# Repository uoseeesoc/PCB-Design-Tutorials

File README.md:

# PCB-Design-Tutorials
This is the repository for the EEE Society PCB Design Tutorials using KiCAD. All of the lecture material and examples can be found here. These sessions were run during the Summer Term of the 2018/19 academic year.

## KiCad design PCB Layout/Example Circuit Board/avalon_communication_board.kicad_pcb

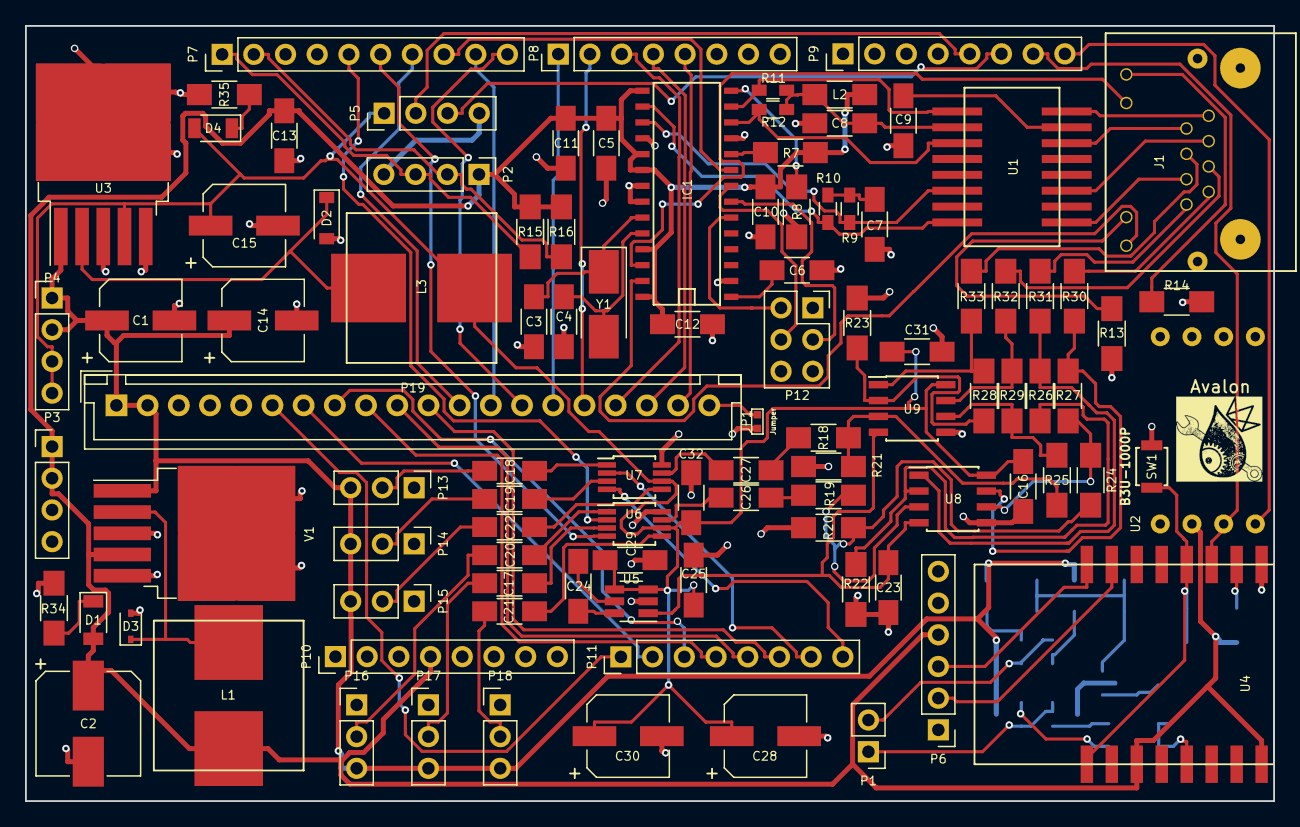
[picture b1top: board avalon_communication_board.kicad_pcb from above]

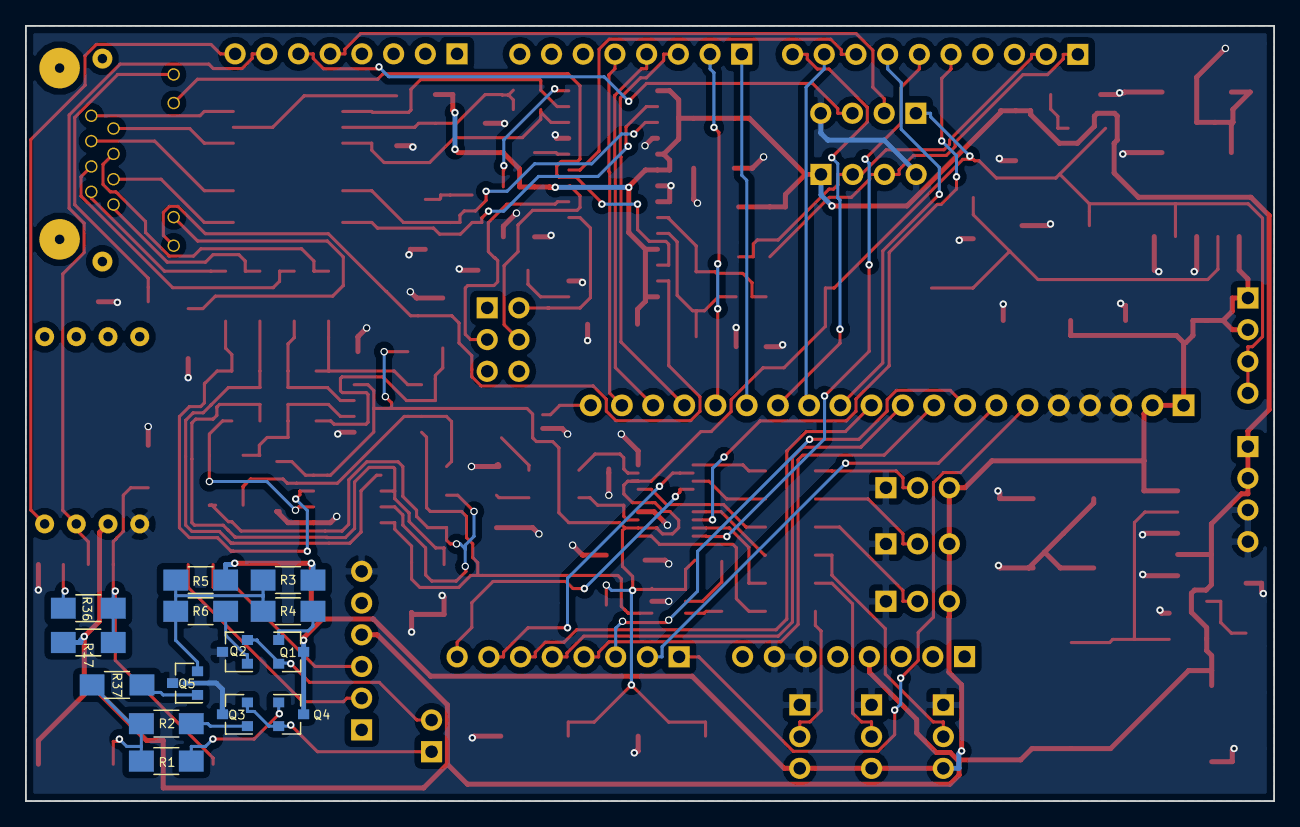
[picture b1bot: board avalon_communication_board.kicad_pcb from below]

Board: 4 copper layers, 100.0 x 62.1 mm, 115 parts (14 on the bottom side), 103 nets.

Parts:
C1, C14: 100uF; CP_Elec_6.3x7.7
C2: 1000uF; CP_Elec_8x10
C3, C4: 18pF; C_1206_HandSoldering
C5, C10, C11, C12, C17, C18, C19, C20, C21, C22, C25, C29, C31, C32: 0.1uF; C_1206_HandSoldering
C6: 10uF; C_1206_HandSoldering
C7, C8: 10nF; C_1206_HandSoldering
C9: 1nF; C_1206_HandSoldering
C13: 100nF; C_1206_HandSoldering
C15: 330uF; CP_Elec_6.3x7.7
C16, C23: 2.2uF; C_1206_HandSoldering
C24: 1uF; C_1206_HandSoldering
C26, C27: 470uF; C_1206_HandSoldering
C28, C30: 47uF; CP_Elec_6.3x7.7
D1: BAT60BE; D_SOD-323
D2: 1N5819; D_SOD-123
D3, D4: LED; D_1206
IC1: ENC28J60-I/SO; SOIC-28
J1: RJ45_LEDS; RJHSE-5381
JP1: Jumper; 0402
L1: 100uH; MSS1278T-334KLD
L2: Ferrite_Bead; R_1206_HandSoldering
L3: 330uH; MSS1278T-334KLD
P1: MC34629; Socket_Strip_Straight_1x02_Pitch2.54mm
P2, P3, P4, P5: MC34633; Socket_Strip_Straight_1x04_Pitch2.54mm
P6: 6 Pin SIL; Socket_Strip_Straight_1x06_Pitch2.54mm
P7: 10 Pin SIL; Socket_Strip_Straight_1x10_Pitch2.54mm
P8, P9, P10, P11: 8 Pin SIL; Socket_Strip_Straight_1x08_Pitch2.54mm
P12: 2x3 Pin SIL; Socket_Strip_Straight_2x03_Pitch2.54mm
P13, P14, P15, P16, P17, P18: MC34631; Socket_Strip_Straight_1x03_Pitch2.54mm
P19: Power Board Connector; JST_XH_B20B-XH-A_20x2.50mm_Straight
Q1, Q4: FMMT597; SOT-23
Q2, Q3, Q5: BC817; SOT-23
R1, R2, R4, R5, R24, R25, R37: 1.5K; R_1206_HandSoldering
R3, R6: 1K; R_1206_HandSoldering
R7, R17, R36: 100K; R_1206_HandSoldering
R8: 2K; R_1206_HandSoldering
R9, R10, R11, R12: 50R; R_0603_HandSoldering
R13, R14, R34: 100R; R_1206_HandSoldering
R15, R16: 10K; R_1206_HandSoldering
R18, R19, R20, R21: 75R; R_1206_HandSoldering
R22, R23, R26, R27, R28, R29: 3K; R_1206_HandSoldering
R30, R31, R32, R33: 43R; R_1206_HandSoldering
R35: 220R; R_1206_HandSoldering
SW1: B3U-1000P
U1: B78476A8247A003
U2: MPU9250
U3: LM2575S; TO-263-5_TabPin3
U4: ESP-12S; ESP12
U5: LM2776; SOT-23-6_Handsoldering
U6, U7: BH76330FVM; MSOP-8_3x3mm_Pitch0.65mm
U8, U9: LMH6643; SOIC-8_3.9x4.9mm_Pitch1.27mm
V1: LM2576; TO-263-5_TabPin3
Y1: ABM3-25MHz; Crystal_SMD_5032-2pin_5.0x3.2mm_HandSoldering

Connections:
+3V3: C2.1, C5.1, C10.1, C11.1, C12.1, C13.1, D3.2, IC1.15, IC1.19, IC1.20, IC1.25, IC1.28, L1.2, L2.1, P2.1, P3.1, P3.2, P6.4, P10.4, R7.1, R15.1, R16.1, R17.1, U2.3, U4.3, U4.8, V1.4
+5V: C15.1, C16.1, C25.1, C28.1, C29.1, C30.1, C31.1, C32.1, D4.2, L3.1, P4.3, P4.4, P5.1, U3.4, U5.3, U5.4, U6.6, U7.6, U8.8, U9.8
+12V: C1.1, C14.1, P4.1, P4.2, P13.3, P14.3, P15.3, P16.3, P17.3, P18.3, P19.1, P19.2, Q1.3, Q4.3, R3.1, R6.1, U3.1, V1.1
-5V: C23.1, U5.1, U8.4, U9.4
BLUE_RX: P5.2, P9.5
BLUE_TX: P5.3, P9.6
CAM1A: J1.8, R31.1
CAM1B: J1.7, R30.1
CAM2A: J1.4, R33.1
CAM2B: J1.5, R32.1
ESP_SCL: P9.8, U2.1
ESP_SDA: P9.7, U2.2, U4.11
Ether_CS': IC1.9, P7.8
Ether_SCK: IC1.8, P12.4
Ether_SI: IC1.7, P12.3
Ether_SO: IC1.6, P12.2
GND: C1.2, C2.2, C3.2, C4.2, C5.2, C6.2, C7.2, C8.2, C9.2, C10.2, C11.2, C12.2, C13.2, C14.2, C15.2, C16.2, C23.2, C25.2, C28.2, C29.2, C30.2, C31.2, C32.2, D1.2, D2.2, IC1.2, IC1.11, IC1.18, IC1.21, IC1.22, JP1.2, P2.4, P3.3, P3.4, P5.4, P6.6, P10.6, P10.7, P13.1, P14.1, P15.1, P16.1, P17.1, P18.1, P19.3, P19.4, P19.5, Q2.3, Q3.3, Q5.3, R8.2, R13.2, R14.1, R20.2, R21.2, R22.2, R23.2, R34.2, R35.2, SW1.1, U2.4, U3.3, U3.5, U4.9, U5.2, U6.8, U7.8, U8.5, U9.5, V1.3, V1.5
GPIO_11: P7.7, P19.12
GPIO_12: P7.6, U6.4
GPIO_13: P7.5, U6.2
GPIO_54: P11.1, P19.6
GPIO_55: P11.2, P19.7
GPIO_56: P11.3, P19.8
GPIO_57: P11.4, P19.9
GPIO_58: P11.5, P19.10
GPIO_59: P11.6, P19.11
GPIO_60: P11.7, U7.2
GPIO_61: P11.8, U7.4
LEDA: IC1.27, J1.12
LEDB: IC1.26, J1.10
unnamed: C3.1, IC1.23, Y1.1
unnamed: C4.1, IC1.24, Y1.2
unnamed: C6.1, IC1.1
unnamed: C7.1, R9.2, R10.1
unnamed: C8.1, L2.2, R11.2, R12.1, U1.2
unnamed: C9.1, U1.15
unnamed: C17.1, U6.3
unnamed: C17.2, P17.2
unnamed: C18.1, U7.1
unnamed: C18.2, P13.2
unnamed: C19.1, P15.2
unnamed: C19.2, U7.5
unnamed: C20.1, P16.2
unnamed: C20.2, U6.1
unnamed: C21.1, U6.5
unnamed: C21.2, P18.2
unnamed: C22.1, U7.3
unnamed: C22.2, P14.2
unnamed: C24.1, U5.6
unnamed: C24.2, U5.5
unnamed: C26.1, U6.7
unnamed: C26.2, R19.1
unnamed: C27.1, U7.7
unnamed: C27.2, R18.1
unnamed: D1.1, L1.1, V1.2
unnamed: D2.1, L3.2, U3.2
unnamed: D3.1, R34.1
unnamed: D4.1, R35.1
unnamed: IC1.10, R7.2
unnamed: IC1.12, R12.2, U1.3
unnamed: IC1.13, R11.1, U1.1
unnamed: IC1.14, R8.1
unnamed: IC1.16, R10.2, U1.8
unnamed: IC1.17, R9.1, U1.6
unnamed: J1.1, U1.16
unnamed: J1.2, U1.14
unnamed: J1.3, U1.11
unnamed: J1.6, U1.9
unnamed: J1.9, R14.2
unnamed: J1.11, R13.1
unnamed: JP1.1, P19.20
unnamed: P1.1, Q3.2, Q4.2
unnamed: P1.2, Q1.2, Q2.2
unnamed: P6.2, U4.15
unnamed: P6.3, U4.16
unnamed: Q1.1, R4.1
unnamed: Q2.1, R5.2
unnamed: Q3.1, R2.2
unnamed: Q4.1, R1.1
unnamed: Q5.1, R37.2
unnamed: Q5.2, R3.2, R4.2, R5.1, R6.2
unnamed: R17.2, R36.2, SW1.2, U4.1, U4.12
unnamed: R18.2, R21.1, R25.2, U9.3
unnamed: R19.2, R20.1, R24.2, U8.3
unnamed: R22.1, R26.2, U8.2
unnamed: R23.1, R28.2, U9.2
unnamed: R24.1, R27.2, U8.6
unnamed: R25.1, R29.2, U9.6
unnamed: R26.1, R31.2, U8.1
unnamed: R27.1, R30.2, U8.7
unnamed: R28.1, R33.2, U9.1
unnamed: R29.1, R32.2, U9.7
unnamed: R36.1, U4.10
POW_PWM_0: P7.9, P19.13
POW_PWM_1: P7.10, P19.14
POW_PWM_2: P8.1, P19.15
POW_PWM_3: P8.2, P19.16
POW_PWM_4: P8.3, P19.17
POW_PWM_5: P8.4, P19.18
POW_PWM_6: P8.5, P19.19
P_SCL: P2.3, P7.1, R15.2
P_SDA: P2.2, P7.2, R16.2
ULTRA_CTRL: R1.2, R2.1, R37.1, U4.5

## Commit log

2019-02-28 - Added the Schematic Capture Lecture slides.
2019-03-16 - Added Component Selection and Footprint Lecture - Added PCB Layout Lecture - Added Example Circuit Board
